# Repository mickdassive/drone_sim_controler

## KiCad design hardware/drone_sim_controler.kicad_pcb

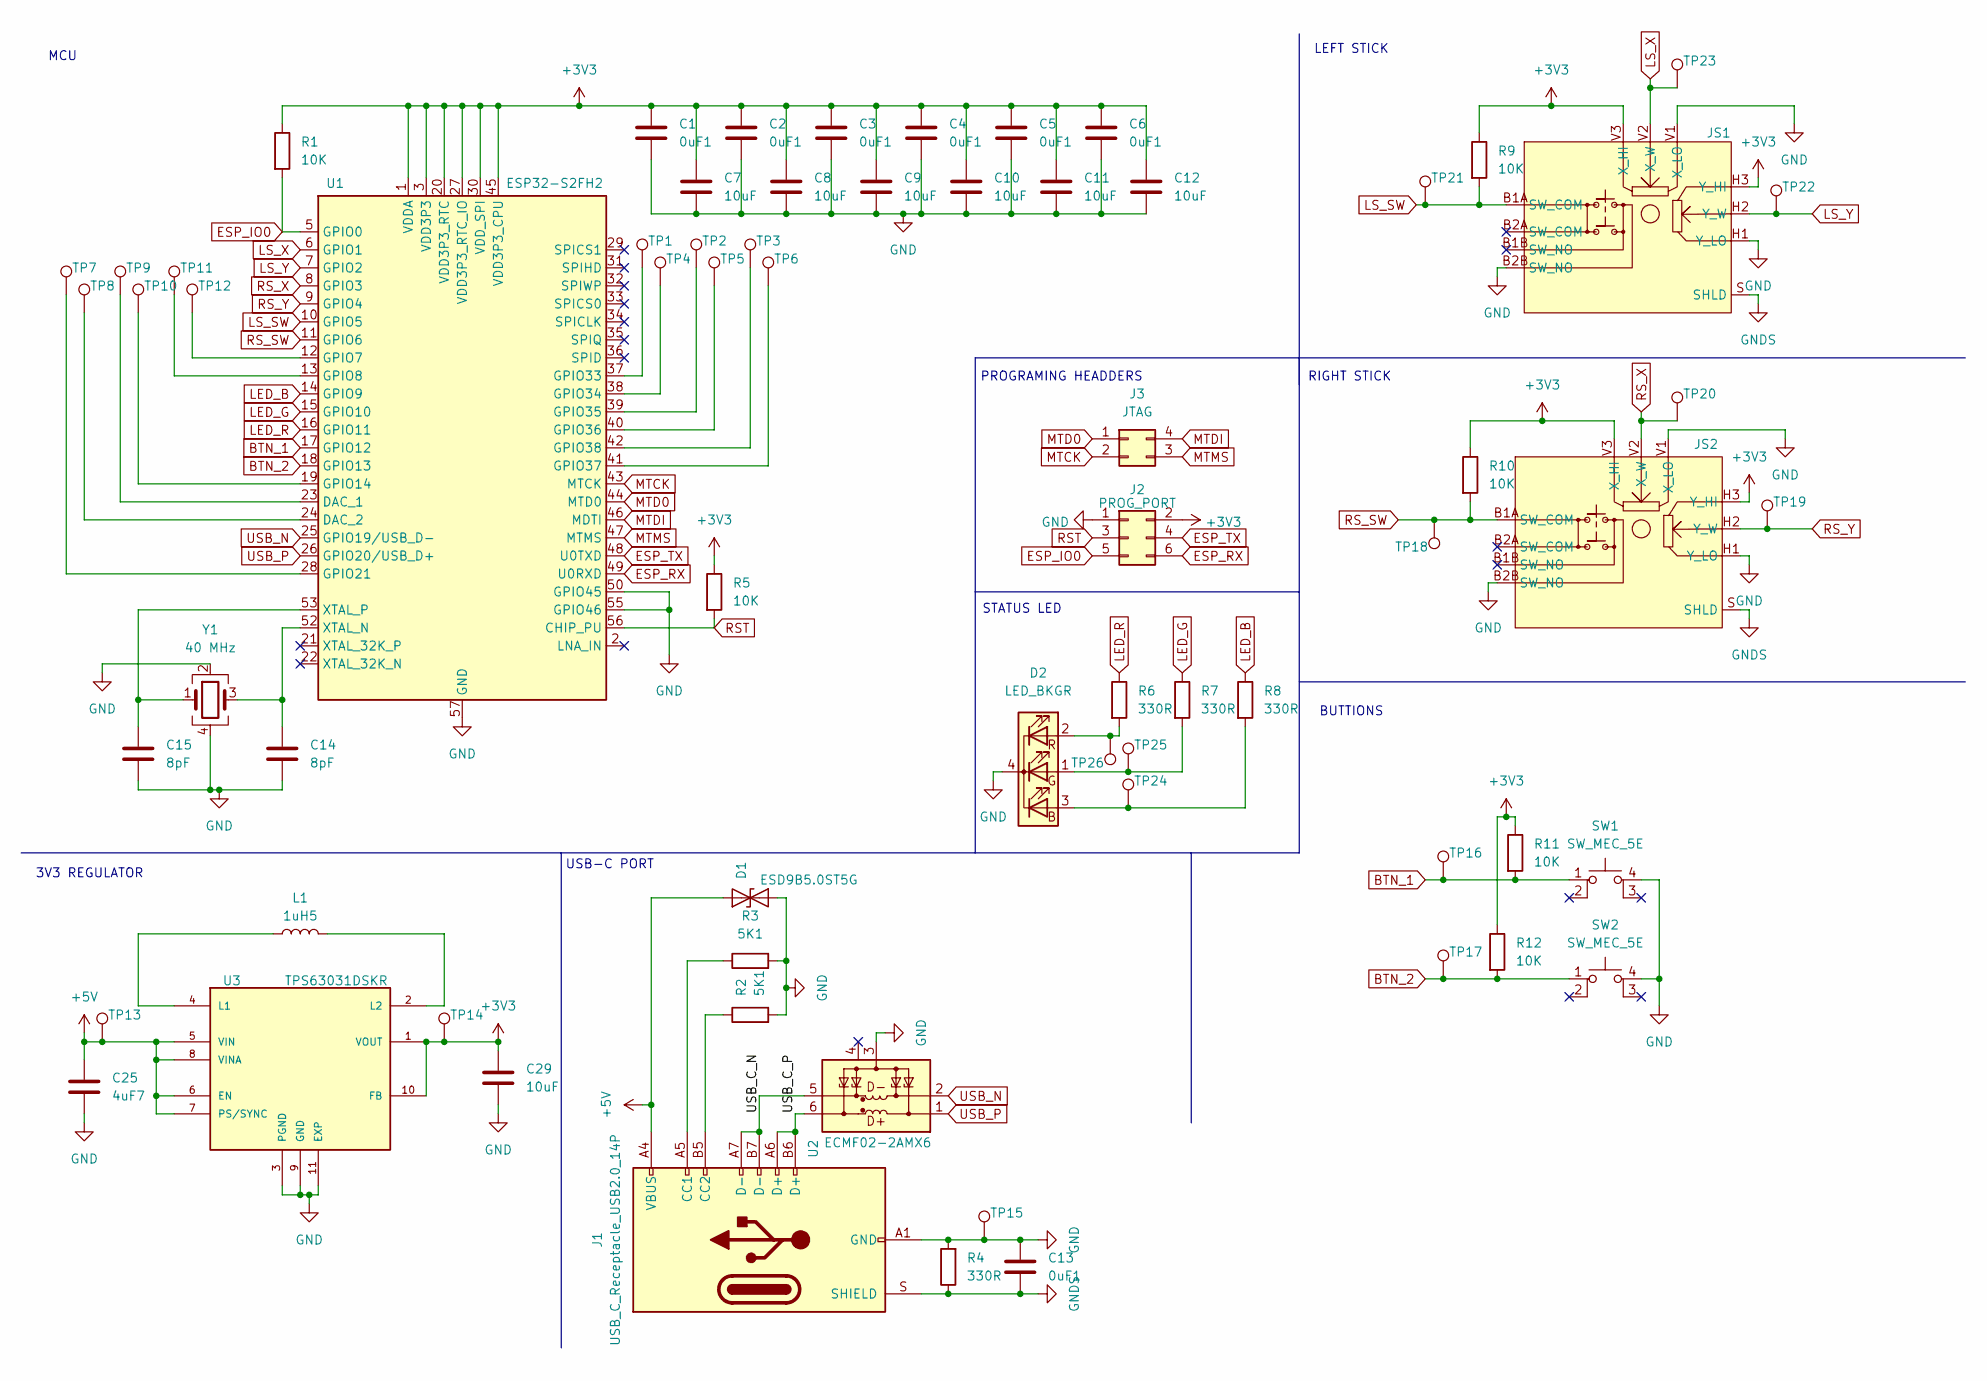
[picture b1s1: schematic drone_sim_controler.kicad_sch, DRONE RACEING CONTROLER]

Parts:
C1, C2, C3, C4, C5, C6, C13: 0uF1; C_0603_1608Metric; DIGIKEY PART # 399-C0603C104M5RACTUCT-ND
C7, C8, C9, C10, C11, C12: 10uF; C_0603_1608Metric; DIGIKEY PART # 1276-1038-1-ND
C14, C15: 8pF; C_0603_1608Metric; DIGIKEY PART # 4713-CHV0603N2508R2BCT-ND
C25: 4uF7; C_0603_1608Metric; Digikey Part Number 1276-1044-1-ND
C29: 10uF; C_0603_1608Metric; Digikey Part Number 1276-1038-1-ND
D1: ESD9B5.0ST5G; D_SOD-923; DIGIKEY PART # ESD9B5.0ST5GOSCT-ND
D2: LED_BKGR; EAST1616RGBA1; DIGIKEY PART # 1080-EAST1616RGBA1CT-ND
J1: USB_C_Receptacle_USB2.0_14P; usb4500; DIGIKEY PART # 2073-USB4500-03-0-ACT-ND
J2: PROG_PORT; PinHeader_2x03_P2.54mm_Vertical
J3: JTAG; PinHeader_2x02_P2.54mm_Vertical
JS1, JS2: PS4_joystick
L1: 1uH5; L_1210_3225Metric; Digikey Part Number 587-3028-1-ND
R1, R5, R9, R10, R11, R12: 10K; R_0603_1608Metric; DIGIKEY PART # RMCF0603JT10K0CT-ND
R2, R3: 5K1; R_0603_1608Metric; DIGIKEY PART # 541-4030-1-ND
R4, R6, R7, R8: 330R; R_0603_1608Metric; DIGIKEY PART # 541-4026-1-ND
SW1, SW2: SW_MEC_5E; SW_PUSH_6mm
TP1, TP2, TP3, TP4, TP5, TP6, TP7, TP8, TP9, TP10, TP11, TP12, TP13, TP14, TP15, TP16, TP17, TP18, TP19, TP20, TP21, TP22, TP23, TP24, TP25, TP26: TestPoint_Pad_D1.0mm
U1: ESP32-S2FH2; QFN-56-1EP_7x7mm_P0.4mm_EP4x4mm; DIGIKEY PART # 1904-ESP32-S2FH2CT-ND
U2: ECMF02-2AMX6; ST_UQFN-6L_1.5x1.7mm_P0.5mm; DIGIKEY PART # 497-10773-1-ND
U3: TPS63031DSKR; PARTREV D; Digikey Part Number 296-39461-1-ND
Y1: 40 MHz; cx3225sa_e

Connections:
+3V3: C1.1, C2.1, C3.1, C4.1, C5.1, C6.1, C7.1, C8.1, C9.1, C10.1, C11.1, C12.1, C29.1, J2.2, JS1.H3 (Y_HI), JS1.V3 (X_HI), JS2.H3 (Y_HI), JS2.V3 (X_HI), R1.1, R5.1, R9.1, R10.1, R11.1, R12.1, TP14.1, U1.1 (VDDA), U1.3 (VDD3P3), U1.4 (VDD3P3), U1.20 (VDD3P3_RTC), U1.27 (VDD3P3_RTC_IO), U1.30 (VDD_SPI), U1.45 (VDD3P3_CPU), U1.51 (VDDA), U1.54 (VDDA), U3.1 (VOUT), U3.10 (FB)
+5V: C25.1, D1.2 (A2), J1.A4 (VBUS), J1.A9 (VBUS), J1.B4 (VBUS), J1.B9 (VBUS), TP13.1, U3.5 (VIN), U3.6 (EN), U3.7 (PS/SYNC), U3.8 (VINA)
/USB_C_N: J1.A7 (D-), J1.B7 (D-), U2.5 (D-_out)
/USB_C_P: J1.A6 (D+), J1.B6 (D+), U2.6 (D+_out)
BTN_1: R11.2, SW1.1, TP16.1, U1.17 (GPIO12)
BTN_2: R12.2, SW2.1, TP17.1, U1.18 (GPIO13)
ESP_IO0: J2.5, R1.2, U1.5 (GPIO0)
ESP_RX: J2.6, U1.49 (U0RXD)
ESP_TX: J2.4, U1.48 (U0TXD)
GND: C1.2, C2.2, C3.2, C4.2, C5.2, C6.2, C7.2, C8.2, C9.2, C10.2, C11.2, C12.2, C13.2, C14.2, C15.2, C25.2, C29.2, D1.1 (A1), D2.4 (K), J1.A1 (GND), J1.A12 (GND), J1.B1 (GND), J1.B12 (GND), J2.1, JS1.B2B (SW_NO), JS1.H1 (Y_LO), JS1.V1 (X_LO), JS2.B2B (SW_NO), JS2.H1 (Y_LO), JS2.V1 (X_LO), R2.2, R3.2, R4.2, SW1.4 (A), SW2.4 (A), TP15.1, U1.50 (GPIO45), U1.55 (GPIO46), U1.57 (GND), U2.3 (GND), U3.3 (PGND), U3.9 (GND), U3.11 (EXP), Y1.2, Y1.4
GNDS: C13.1, J1.S (SHIELD), JS1.S (SHLD), JS2.S (SHLD), R4.1
LED_B: R8.1, U1.14 (GPIO9)
LED_G: R7.1, U1.15 (GPIO10)
LED_R: R6.1, U1.16 (GPIO11)
LS_SW: JS1.B1A (SW_COM), R9.2, TP21.1, U1.10 (GPIO5)
LS_X: JS1.V2 (X_W), TP23.1, U1.6 (GPIO1)
LS_Y: JS1.H2 (Y_W), TP22.1, U1.7 (GPIO2)
MTCK: J3.2, U1.43 (MTCK)
MTD0: J3.1, U1.44 (MTD0)
MTDI: J3.4, U1.46 (MDTI)
MTMS: J3.3, U1.47 (MTMS)
unnamed: D2.3 (BA), R8.2, TP24.1
unnamed: D2.1 (GA), R7.2, TP25.1
unnamed: D2.2 (RA), R6.2, TP26.1
unnamed: J1.A5 (CC1), R3.1
unnamed: J1.B5 (CC2), R2.1
unnamed: TP9.1, U1.23 (DAC_1)
unnamed: TP8.1, U1.24 (DAC_2)
unnamed: TP12.1, U1.12 (GPIO7)
unnamed: TP11.1, U1.13 (GPIO8)
unnamed: TP10.1, U1.19 (GPIO14)
unnamed: TP7.1, U1.28 (GPIO21)
unnamed: TP1.1, U1.37 (GPIO33)
unnamed: TP4.1, U1.38 (GPIO34)
unnamed: TP2.1, U1.39 (GPIO35)
unnamed: TP5.1, U1.40 (GPIO36)
unnamed: TP6.1, U1.41 (GPIO37)
unnamed: TP3.1, U1.42 (GPIO38)
unnamed: C14.1, U1.52 (XTAL_N), Y1.3
unnamed: C15.1, U1.53 (XTAL_P), Y1.1
unnamed: L1.1, U3.4 (L1)
unnamed: L1.2, U3.2 (L2)
RST: J2.3, R5.2, U1.56 (CHIP_PU)
RS_SW: JS2.B1A (SW_COM), R10.2, TP18.1, U1.11 (GPIO6)
RS_X: JS2.V2 (X_W), TP20.1, U1.8 (GPIO3)
RS_Y: JS2.H2 (Y_W), TP19.1, U1.9 (GPIO4)
USB_N: U1.25 (GPIO19/USB_D-), U2.2 (D-_in)
USB_P: U1.26 (GPIO20/USB_D+), U2.1 (D+_in)

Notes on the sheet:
USB-C PORT
RIGHT STICK
PROGRAMING HEADDERS
3V3 REGULATOR
STATUS LED
LEFT STICK
MCU
BUTTIONS

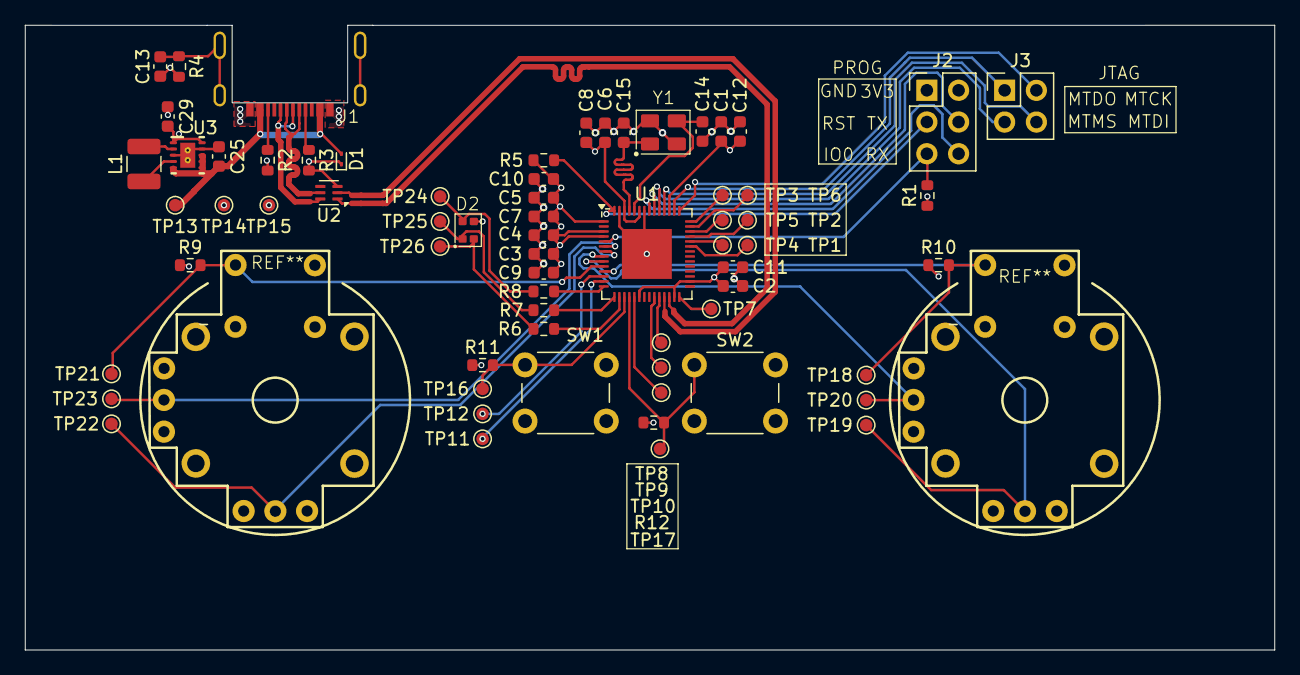
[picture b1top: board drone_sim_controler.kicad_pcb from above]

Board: 4 copper layers, 100.0 x 50.0 mm, 69 parts (0 on the bottom side), 48 nets.

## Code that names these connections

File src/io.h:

#ifndef io_h
#define io_h

#include <Arduino.h>

//io_init struct setup
enum in_out {
    in,       //input
    out,      //output
    analog,   //analog pin
    led,      //led pin
    usb       //usb pin
  };
  
  struct pin {
    uint8_t pin_number;        //gpio number
    in_out pin_mode;       //defines pinmode see enum above for deatails
      
  };
  //BE SURE TO ADD PINS TO BOTH THE "pin" STRUCT AND THE "pin_names" ARRAY THEY MUST MATCH
  //io_init struct defines  {pin_number, pin_mode}
  static struct pin gpio0 {0, in};
  static struct pin ls_x {1, analog};
  static struct pin ls_y {2, analog};
  static struct pin rs_x {3, analog};
  static struct pin rs_y {4, analog};
  static struct pin ls_sw {5, in};
  static struct pin rs_sw {6, in};
  static struct pin gpio7 {7, in};
  static struct pin gpio8 {8, in};
  static struct pin led_b {9, led};
  static struct pin led_g {10, led};
  static struct pin led_r {11, led};
  static struct pin btn_1 {12, in};
  static struct pin btn_2 {13, in};
  static struct pin gpio14 {14, in};
  static struct pin dac_1 {17, out};
  static struct pin dac_2 {18, out};
  static struct pin usb_dn {19, usb};
  static struct pin usb_dp {20, usb};
  static struct pin gpio21 {21, in};
  static struct pin gpi033 {33, in};
  static struct pin gpio34 {34, in};
  static struct pin gpio35 {35, in};
  static struct pin gpio36 {36, in};
  static struct pin gpio37 {37, in};
  static struct pin gpio38 {38, in};


   
  
  //Array of pin structs for automatic pin initialization
static struct pin* pin_names[] = {
    &gpio0,
    &ls_x,
    &ls_y,
    &rs_x,
    &rs_y,
    &ls_sw,
    &rs_sw,
    &gpio7,
    &gpio8,
    &led_b,
    &led_g,
    &led_r,
    &btn_1,
    &btn_2,
    &gpio14,
    &dac_1,
    &dac_2,
    &usb_dn,
    &usb_dp,
    &gpio21,
    &gpi033,
    &gpio34,
    &gpio35,
    &gpio36,
    &gpio37,
    &gpio38
};

struct controler_data {
    int16_t ls_x;
    int16_t ls_y;
    int16_t rs_x;
    int16_t rs_y;
    uint32_t buttons;
};
//struct to hold controler data
extern struct controler_data current_gamepad_data;

//function prototypes
void io_gpio_init();
struct controler_data io_read_gamepad_data();

#endif // io_h

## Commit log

2025-04-30 setting up project
2025-04-30 first rev of schmatic
2025-05-07 compleeted first rev of board
2025-05-07 working on implimenting usb
2025-05-08 pulling my hair out with usb
2025-05-22 finaly got usb working
2025-05-22 added basic led functionality
2025-05-22 regerated pcb files
2025-06-09 trying to setup custom boards
2025-07-03 upolad for platformio forums
2025-07-04 got debugging and uploading working corectly
